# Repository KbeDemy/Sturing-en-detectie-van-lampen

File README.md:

# I2C Uitbreiding bord - Lamp sturing & Detectie

Expansion board voor lampenbeheer. Bedoeld voor gebruik met een externe microcontroller (ESP32) via I2C.

## Specificaties
- **I/O Expander:** MCP23017 (I2C) 
- **Input:** 230V AC detectie via LTV-814 optocouplers.
- **Output:** 30V AC sturing voor Eltako relais via Omron G5V-1 relais.
- **Indicatie:** Debug-LED's voor logica en relaisstatus.

## Pinout & Adressen
- **I2C Adres:** Standaard 0x20 (instelbaar via A0, A1, A2).
- **Signaal/voeding - niveaus:** 
    - 3.3VDC logic
    - 5VDC aansturen relais
    - 30VAC aansturen eltako
    - 230VAC uitlezen status lamp
- **MCP GPA 0-7:** INPUT
- **MCP GPB 0-7:** OUTPUT

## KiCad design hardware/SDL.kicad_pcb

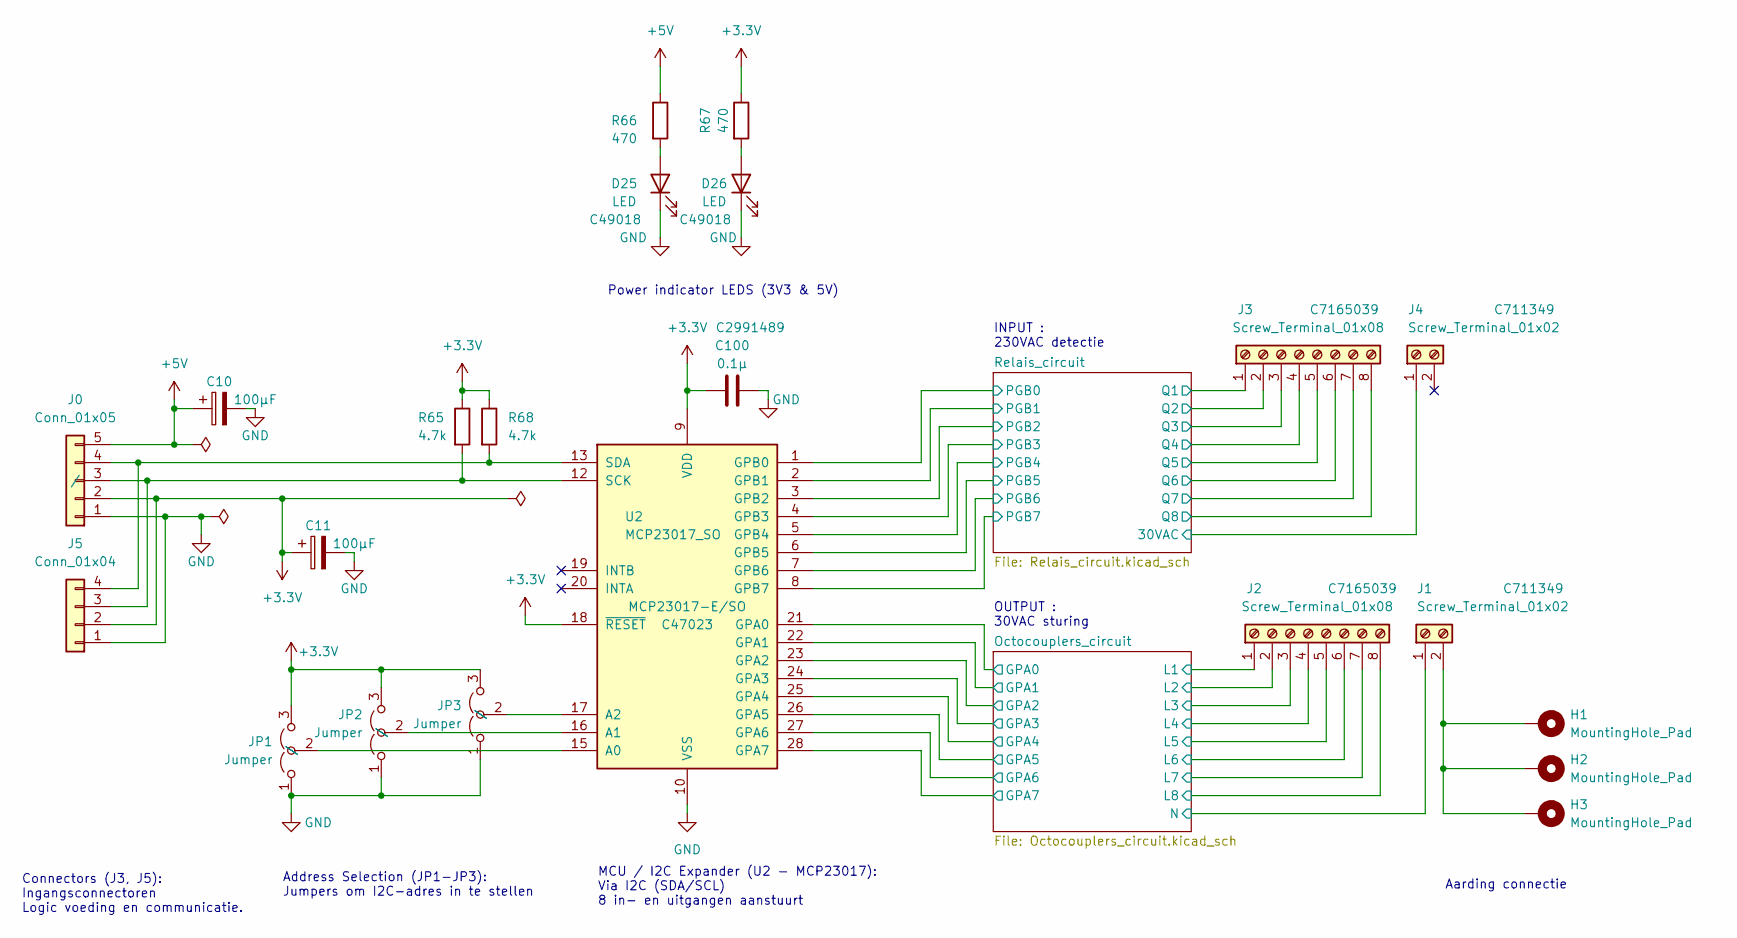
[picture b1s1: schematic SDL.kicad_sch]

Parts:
C10, C11: 100µF; CP_Radial_D4.0mm_P1.50mm
C100: 0.1µ; C_0603_1608Metric; JLCPCB C2991489
D25, D26: LED; LED_0603_1608Metric; JLCPCB C49018
H1, H2, H3: MountingHole_Pad; MountingHole_2.2mm_M2_DIN965_Pad_TopBottom
J0: Conn_01x05; PinSocket_1x05_P2.54mm_Vertical; MPN /; JLCPCB /
J1, J4: Screw_Terminal_01x02; TerminalBlock_Phoenix_MKDS-1,5-2-5.08_1x02_P5.08mm_Horizont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; MPN 1715721; JLCPCB C711349
J2, J3: Screw_Terminal_01x08; TerminalBlock_Phoenix_MKDS-1,5-8-5.08_1x08_P5.08mm_Horizont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; MPN 1715789; JLCPCB C7165039
J5: Conn_01x04; PinHeader_1x04_P2.54mm_Vertical
JP1, JP2, JP3: Jumper; SolderJumper-3_P1.3mm_Open_RoundedPad1.0x1.5mm_NumberLabels; MPN /; JLCPCB /
R65, R68: 4.7k; R_0603_1608Metric
R66, R67: 470; R_0603_1608Metric
U2: MCP23017_SO; SOIC-28W_7.5x17.9mm_P1.27mm; MPN MCP23017-E/SO; JLCPCB C47023

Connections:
+3.3V: C11.1, C100.1, J0.2, J5.2, JP1.3 (B), JP2.3 (B), JP3.3 (B), R65.1, R67.1, R68.1, U2.9 (VDD), U2.18 (~RESET); also elsewhere on the board
+5V: C10.1, J0.5, R66.1; also elsewhere on the board
/Octocouplers_circuit/GPA0: U2.21 (GPA0); also elsewhere on the board
/Octocouplers_circuit/GPA1: U2.22 (GPA1); also elsewhere on the board
/Octocouplers_circuit/GPA2: U2.23 (GPA2); also elsewhere on the board
/Octocouplers_circuit/GPA3: U2.24 (GPA3); also elsewhere on the board
/Octocouplers_circuit/GPA4: U2.25 (GPA4); also elsewhere on the board
/Octocouplers_circuit/GPA5: U2.26 (GPA5); also elsewhere on the board
/Octocouplers_circuit/GPA6: U2.27 (GPA6); also elsewhere on the board
/Octocouplers_circuit/GPA7: U2.28 (GPA7); also elsewhere on the board
/Octocouplers_circuit/L1: J2.1; also elsewhere on the board
/Octocouplers_circuit/L2: J2.2; also elsewhere on the board
/Octocouplers_circuit/L3: J2.3; also elsewhere on the board
/Octocouplers_circuit/L4: J2.4; also elsewhere on the board
/Octocouplers_circuit/L5: J2.5; also elsewhere on the board
/Octocouplers_circuit/L6: J2.6; also elsewhere on the board
/Octocouplers_circuit/L7: J2.7; also elsewhere on the board
/Octocouplers_circuit/L8: J2.8; also elsewhere on the board
/Octocouplers_circuit/N: J1.1; also elsewhere on the board
/Relais_circuit/30VAC: J4.1; also elsewhere on the board
/Relais_circuit/PGB0: U2.1 (GPB0); also elsewhere on the board
/Relais_circuit/PGB1: U2.2 (GPB1); also elsewhere on the board
/Relais_circuit/PGB2: U2.3 (GPB2); also elsewhere on the board
/Relais_circuit/PGB3: U2.4 (GPB3); also elsewhere on the board
/Relais_circuit/PGB4: U2.5 (GPB4); also elsewhere on the board
/Relais_circuit/PGB5: U2.6 (GPB5); also elsewhere on the board
/Relais_circuit/PGB6: U2.7 (GPB6); also elsewhere on the board
/Relais_circuit/PGB7: U2.8 (GPB7); also elsewhere on the board
/Relais_circuit/Q1: J3.1; also elsewhere on the board
/Relais_circuit/Q2: J3.2; also elsewhere on the board
/Relais_circuit/Q3: J3.3; also elsewhere on the board
/Relais_circuit/Q4: J3.4; also elsewhere on the board
/Relais_circuit/Q5: J3.5; also elsewhere on the board
/Relais_circuit/Q6: J3.6; also elsewhere on the board
/Relais_circuit/Q7: J3.7; also elsewhere on the board
/Relais_circuit/Q8: J3.8; also elsewhere on the board
GND: C10.2, C11.2, C100.2, D25.1 (K), D26.1 (K), J0.1, J5.1, JP1.1 (A), JP2.1 (A), JP3.1 (A), U2.10 (VSS); also elsewhere on the board
unnamed: D25.2 (A), R66.2
unnamed: D26.2 (A), R67.2
unnamed: J0.3, J5.3, R65.2, U2.12 (SCK)
unnamed: J0.4, J5.4, R68.2, U2.13 (SDA)
unnamed: H1.1, H2.1, H3.1, J1.2
unnamed: JP1.2 (C), U2.15 (A0)
unnamed: JP2.2 (C), U2.16 (A1)
unnamed: JP3.2 (C), U2.17 (A2)

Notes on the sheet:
INPUT : 230VAC detectie
OUTPUT : 30VAC sturing
MCU / I2C Expander (U2 - MCP23017): Via I2C (SDA/SCL) 8 in- en uitgangen aanstuurt
Connectors (J3, J5): Ingangsconnectoren Logic voeding en communicatie.
Address Selection (JP1-JP3): Jumpers om I2C-adres in te stellen
Aarding connectie
Power indicator LEDS (3V3 & 5V)

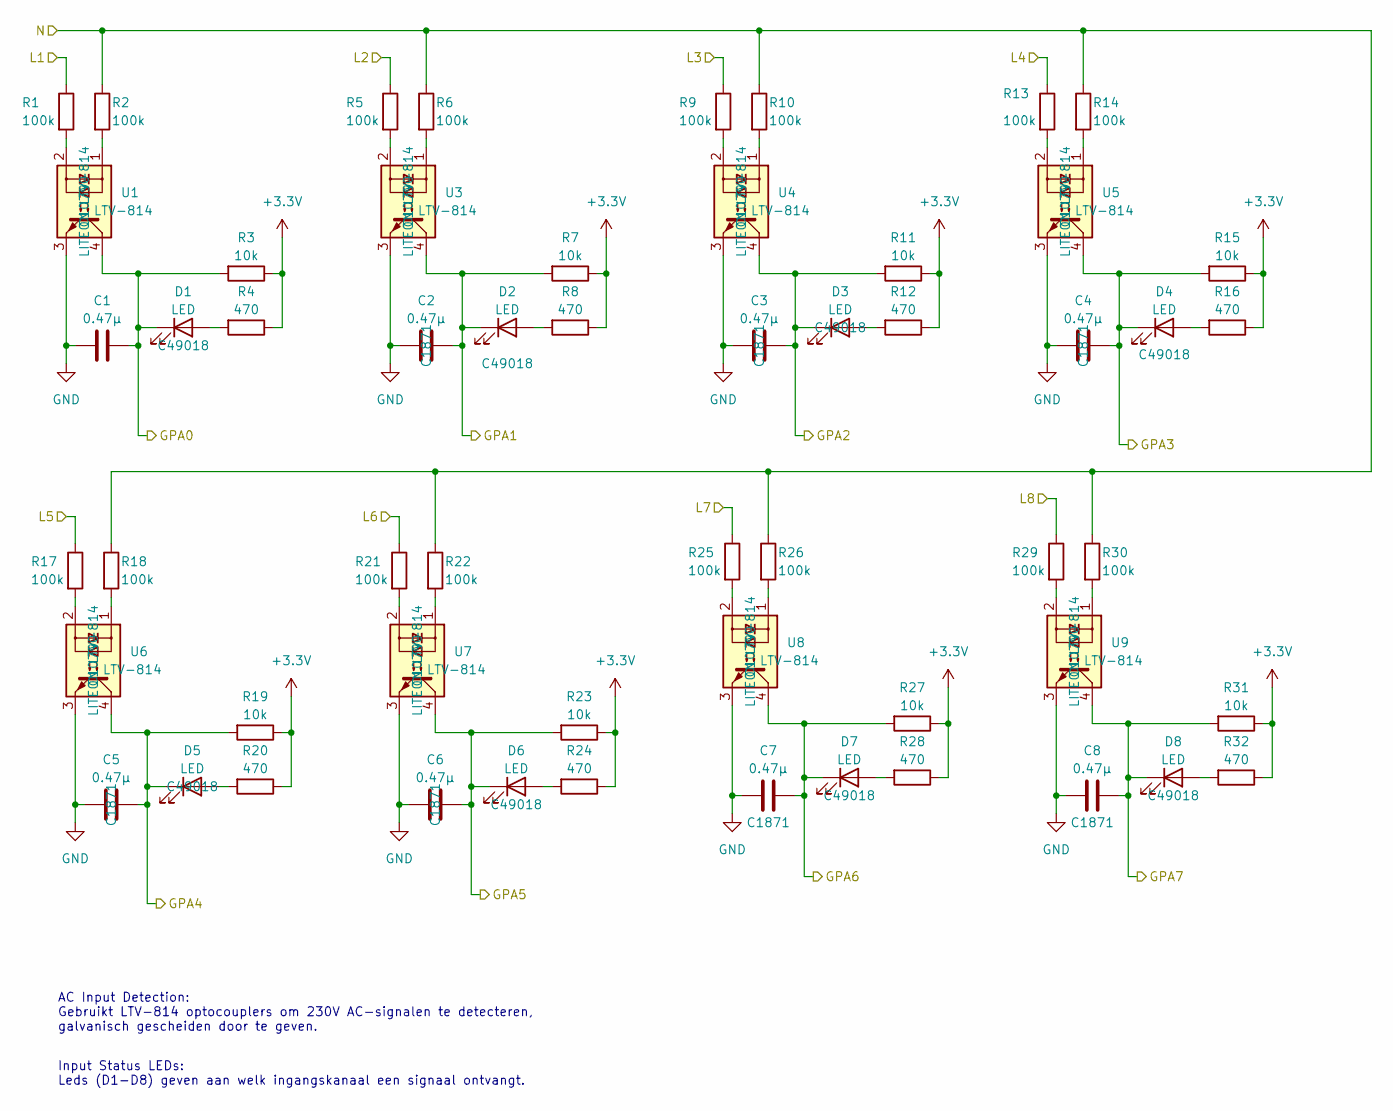
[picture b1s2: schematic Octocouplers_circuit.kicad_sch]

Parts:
C1, C2, C3, C4, C5, C6, C7, C8: 0.47µ; C_0603_1608Metric; JLCPCB C1871
D1, D2, D3, D4, D5, D6, D7, D8: LED; LED_0603_1608Metric; JLCPCB C49018
R1, R2, R5, R6, R9, R10, R13, R14, R17, R18, R21, R22, R25, R26, R29, R30: 100k; R_1206_3216Metric
R3, R7, R11, R15, R19, R23, R27, R31: 10k; R_0603_1608Metric
R4, R8, R12, R16, R20, R24, R28, R32: 470; R_0603_1608Metric
U1, U3, U4, U5, U6, U7, U8, U9: LTV-814; DIP-4_W7.62mm; MPN LITEON LTV-814; JLCPCB C10790

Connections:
+3.3V: R3.1, R4.1, R7.1, R8.1, R11.1, R12.1, R15.1, R16.1, R19.1, R20.1, R23.1, R24.1, R27.1, R28.1, R31.1, R32.1; also elsewhere on the board
/Octocouplers_circuit/GPA0: C1.2, D1.1 (K), R3.2, U1.4; also elsewhere on the board
/Octocouplers_circuit/GPA1: C2.2, D2.1 (K), R7.2, U3.4; also elsewhere on the board
/Octocouplers_circuit/GPA2: C3.2, D3.1 (K), R11.2, U4.4; also elsewhere on the board
/Octocouplers_circuit/GPA3: C4.2, D4.1 (K), R15.2, U5.4; also elsewhere on the board
/Octocouplers_circuit/GPA4: C5.2, D5.1 (K), R19.2, U6.4; also elsewhere on the board
/Octocouplers_circuit/GPA5: C6.2, D6.1 (K), R23.2, U7.4; also elsewhere on the board
/Octocouplers_circuit/GPA6: C7.2, D7.1 (K), R27.2, U8.4; also elsewhere on the board
/Octocouplers_circuit/GPA7: C8.2, D8.1 (K), R31.2, U9.4; also elsewhere on the board
/Octocouplers_circuit/L1: R1.1; also elsewhere on the board
/Octocouplers_circuit/L2: R5.1; also elsewhere on the board
/Octocouplers_circuit/L3: R9.1; also elsewhere on the board
/Octocouplers_circuit/L4: R13.1; also elsewhere on the board
/Octocouplers_circuit/L5: R17.1; also elsewhere on the board
/Octocouplers_circuit/L6: R21.1; also elsewhere on the board
/Octocouplers_circuit/L7: R25.1; also elsewhere on the board
/Octocouplers_circuit/L8: R29.1; also elsewhere on the board
/Octocouplers_circuit/N: R2.1, R6.1, R10.1, R14.1, R18.1, R22.1, R26.1, R30.1; also elsewhere on the board
GND: C1.1, C2.1, C3.1, C4.1, C5.1, C6.1, C7.1, C8.1, U1.3, U3.3, U4.3, U5.3, U6.3, U7.3, U8.3, U9.3; also elsewhere on the board
unnamed: D1.2 (A), R4.2
unnamed: D2.2 (A), R8.2
unnamed: D3.2 (A), R12.2
unnamed: D4.2 (A), R16.2
unnamed: D5.2 (A), R20.2
unnamed: D6.2 (A), R24.2
unnamed: D7.2 (A), R28.2
unnamed: D8.2 (A), R32.2
unnamed: R1.2, U1.2
unnamed: R2.2, U1.1
unnamed: R5.2, U3.2
unnamed: R6.2, U3.1
unnamed: R9.2, U4.2
unnamed: R10.2, U4.1
unnamed: R13.2, U5.2
unnamed: R14.2, U5.1
unnamed: R17.2, U6.2
unnamed: R18.2, U6.1
unnamed: R21.2, U7.2
unnamed: R22.2, U7.1
unnamed: R25.2, U8.2
unnamed: R26.2, U8.1
unnamed: R29.2, U9.2
unnamed: R30.2, U9.1

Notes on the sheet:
AC Input Detection: Gebruikt LTV-814 optocouplers om 230V AC-signalen te detecteren, galvanisch gescheiden door te geven.
Input Status LEDs: Leds (D1-D8) geven aan welk ingangskanaal een signaal ontvangt.

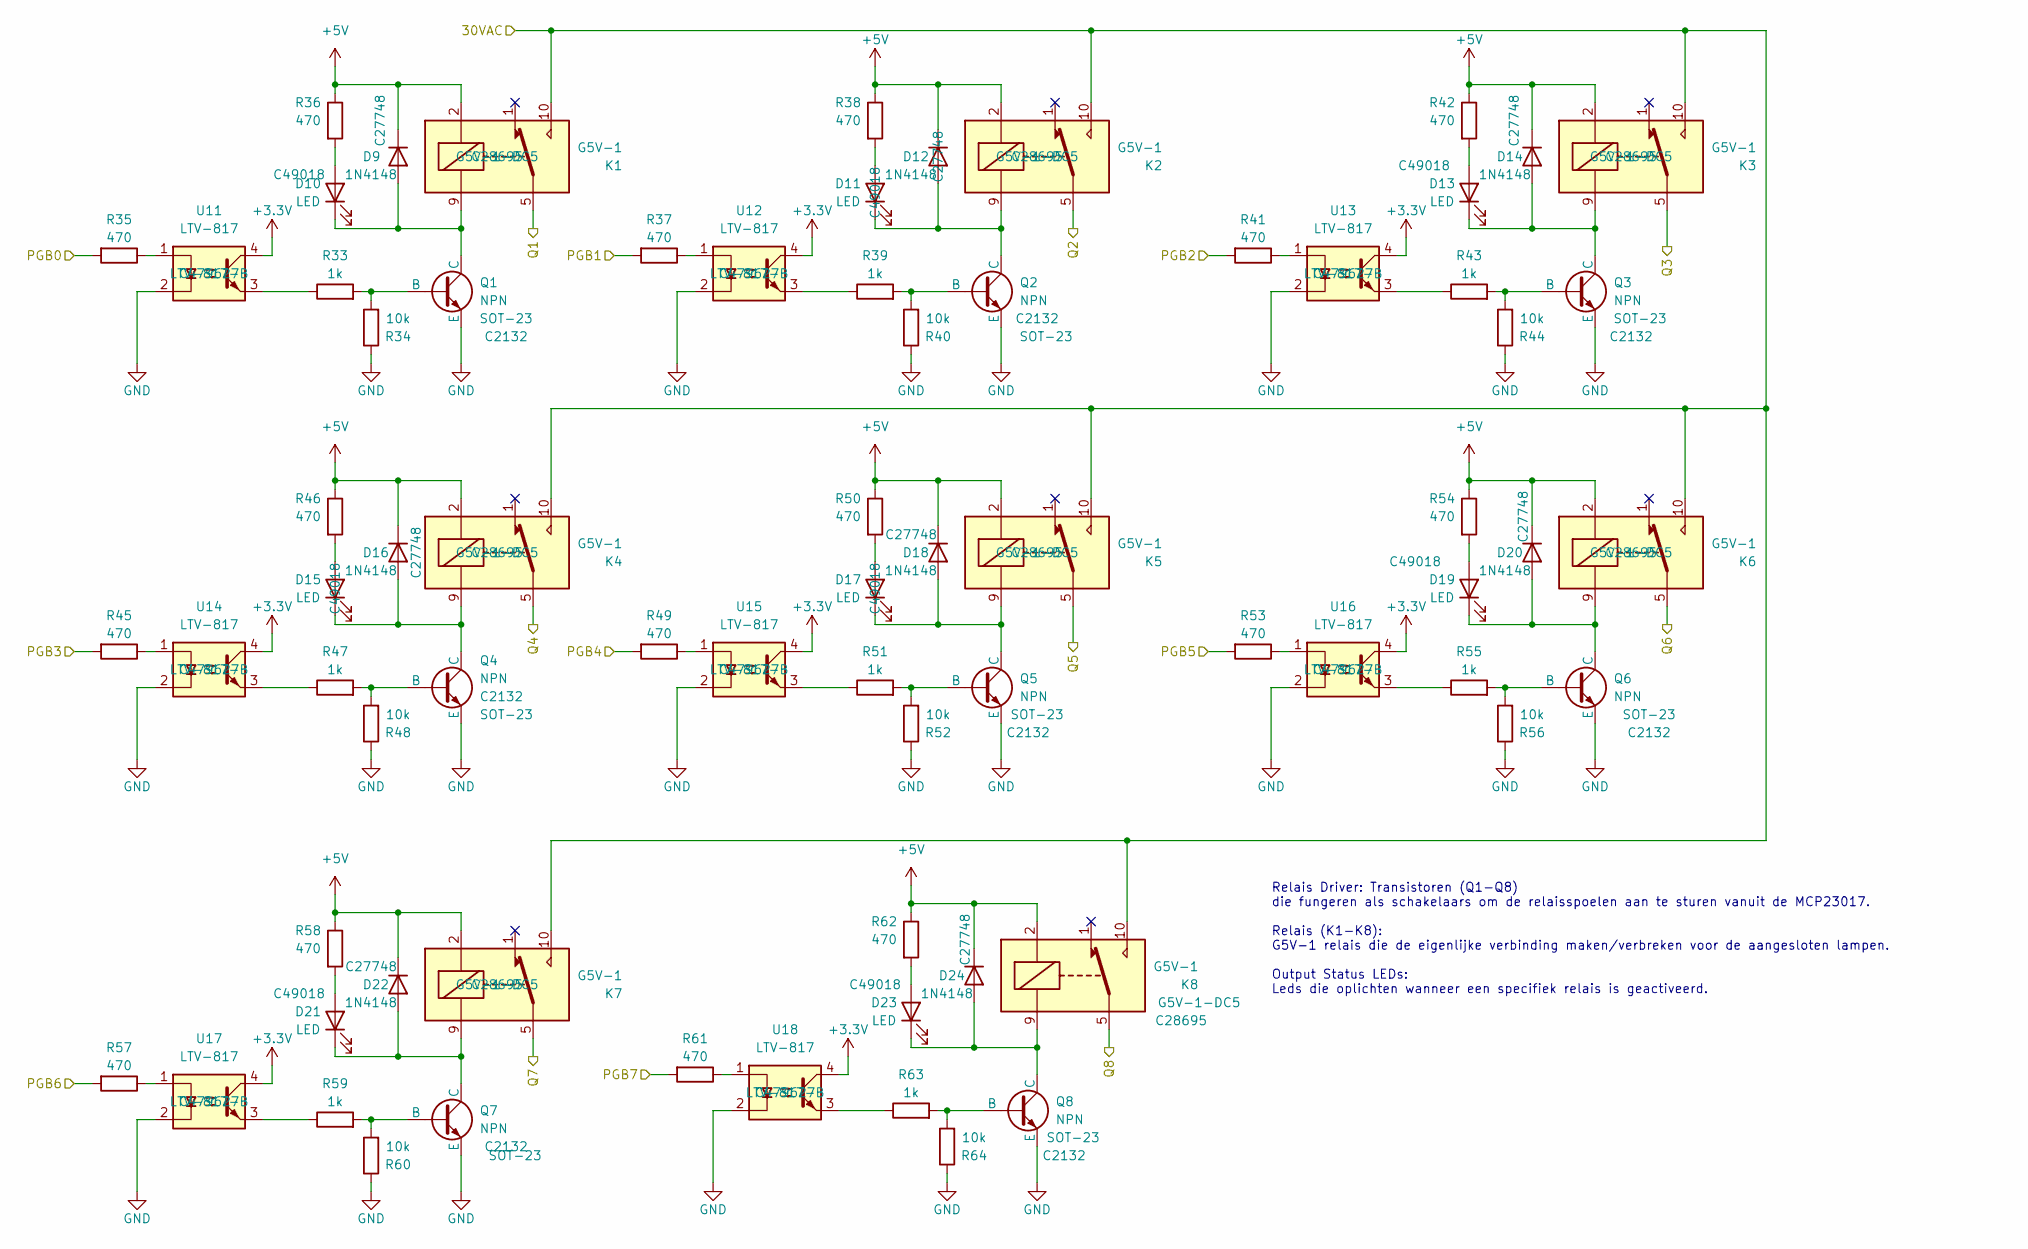
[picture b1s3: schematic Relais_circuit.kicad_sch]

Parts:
D9, D12, D14, D16, D18, D20, D22, D24: 1N4148; D_SOD-523; JLCPCB C27748
D10, D11, D13, D15, D17, D19, D21, D23: LED; LED_0603_1608Metric; JLCPCB C49018
K1, K2, K3, K4, K5, K6, K7, K8: G5V-1; Relay_SPDT_Omron_G5V-1; MPN G5V-1-DC5; JLCPCB C28695
Q1, Q2, Q3, Q4, Q5, Q6, Q7, Q8: NPN; SOT-23; MPN SOT-23; JLCPCB C2132
R33, R39, R43, R47, R51, R55, R59, R63: 1k; R_0603_1608Metric
R34, R40, R44, R48, R52, R56, R60, R64: 10k; R_0603_1608Metric
R35, R36, R37, R38, R41, R42, R45, R46, R49, R50, R53, R54, R57, R58, R61, R62: 470; R_0603_1608Metric
U11, U12, U13, U14, U15, U16, U17, U18: LTV-817; DIP-4_W7.62mm; MPN LTV-817-B; JLCPCB C479627

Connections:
+3.3V: U11.4, U12.4, U13.4, U14.4, U15.4, U16.4, U17.4, U18.4; also elsewhere on the board
+5V: D9.1 (K), D12.1 (K), D14.1 (K), D16.1 (K), D18.1 (K), D20.1 (K), D22.1 (K), D24.1 (K), K1.2, K2.2, K3.2, K4.2, K5.2, K6.2, K7.2, K8.2, R36.1, R38.1, R42.1, R46.1, R50.1, R54.1, R58.1, R62.1; also elsewhere on the board
/Relais_circuit/30VAC: K1.10, K2.10, K3.10, K4.10, K5.10, K6.10, K7.10, K8.10; also elsewhere on the board
/Relais_circuit/PGB0: R35.2; also elsewhere on the board
/Relais_circuit/PGB1: R37.2; also elsewhere on the board
/Relais_circuit/PGB2: R41.2; also elsewhere on the board
/Relais_circuit/PGB3: R45.2; also elsewhere on the board
/Relais_circuit/PGB4: R49.2; also elsewhere on the board
/Relais_circuit/PGB5: R53.2; also elsewhere on the board
/Relais_circuit/PGB6: R57.2; also elsewhere on the board
/Relais_circuit/PGB7: R61.2; also elsewhere on the board
/Relais_circuit/Q1: K1.5, K1.6; also elsewhere on the board
/Relais_circuit/Q2: K2.5, K2.6; also elsewhere on the board
/Relais_circuit/Q3: K3.5, K3.6; also elsewhere on the board
/Relais_circuit/Q4: K4.5, K4.6; also elsewhere on the board
/Relais_circuit/Q5: K5.5, K5.6; also elsewhere on the board
/Relais_circuit/Q6: K6.5, K6.6; also elsewhere on the board
/Relais_circuit/Q7: K7.5, K7.6; also elsewhere on the board
/Relais_circuit/Q8: K8.5, K8.6; also elsewhere on the board
GND: Q1.2 (E), Q2.2 (E), Q3.2 (E), Q4.2 (E), Q5.2 (E), Q6.2 (E), Q7.2 (E), Q8.2 (E), R34.1, R40.1, R44.1, R48.1, R52.1, R56.1, R60.1, R64.1, U11.2, U12.2, U13.2, U14.2, U15.2, U16.2, U17.2, U18.2; also elsewhere on the board
unnamed: D10.2 (A), R36.2
unnamed: D9.2 (A), D10.1 (K), K1.9, Q1.3 (C)
unnamed: D11.2 (A), R38.2
unnamed: D11.1 (K), D12.2 (A), K2.9, Q2.3 (C)
unnamed: D13.2 (A), R42.2
unnamed: D13.1 (K), D14.2 (A), K3.9, Q3.3 (C)
unnamed: D15.2 (A), R46.2
unnamed: D15.1 (K), D16.2 (A), K4.9, Q4.3 (C)
unnamed: D17.2 (A), R50.2
unnamed: D17.1 (K), D18.2 (A), K5.9, Q5.3 (C)
unnamed: D19.2 (A), R54.2
unnamed: D19.1 (K), D20.2 (A), K6.9, Q6.3 (C)
unnamed: D21.2 (A), R58.2
unnamed: D21.1 (K), D22.2 (A), K7.9, Q7.3 (C)
unnamed: D23.2 (A), R62.2
unnamed: D23.1 (K), D24.2 (A), K8.9, Q8.3 (C)
unnamed: Q1.1 (B), R33.2, R34.2
unnamed: Q2.1 (B), R39.2, R40.2
unnamed: Q3.1 (B), R43.2, R44.2
unnamed: Q4.1 (B), R47.2, R48.2
unnamed: Q5.1 (B), R51.2, R52.2
unnamed: Q6.1 (B), R55.2, R56.2
unnamed: Q7.1 (B), R59.2, R60.2
unnamed: Q8.1 (B), R63.2, R64.2
unnamed: R33.1, U11.3
unnamed: R35.1, U11.1
unnamed: R37.1, U12.1
unnamed: R39.1, U12.3
unnamed: R41.1, U13.1
unnamed: R43.1, U13.3
unnamed: R45.1, U14.1
unnamed: R47.1, U14.3
unnamed: R49.1, U15.1
unnamed: R51.1, U15.3
unnamed: R53.1, U16.1
unnamed: R55.1, U16.3
unnamed: R57.1, U17.1
unnamed: R59.1, U17.3
unnamed: R61.1, U18.1
unnamed: R63.1, U18.3

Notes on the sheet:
Relais Driver: Transistoren (Q1-Q8) die fungeren als schakelaars om de relaisspoelen aan te sturen vanuit de MCP23017. Relais (K1-K8): G5V-1 relais die de eigenlijke verbinding maken/verbreken voor de aangesloten lampen. Output Status LEDs: Leds die oplichten wanneer een specifiek relais is geactiv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

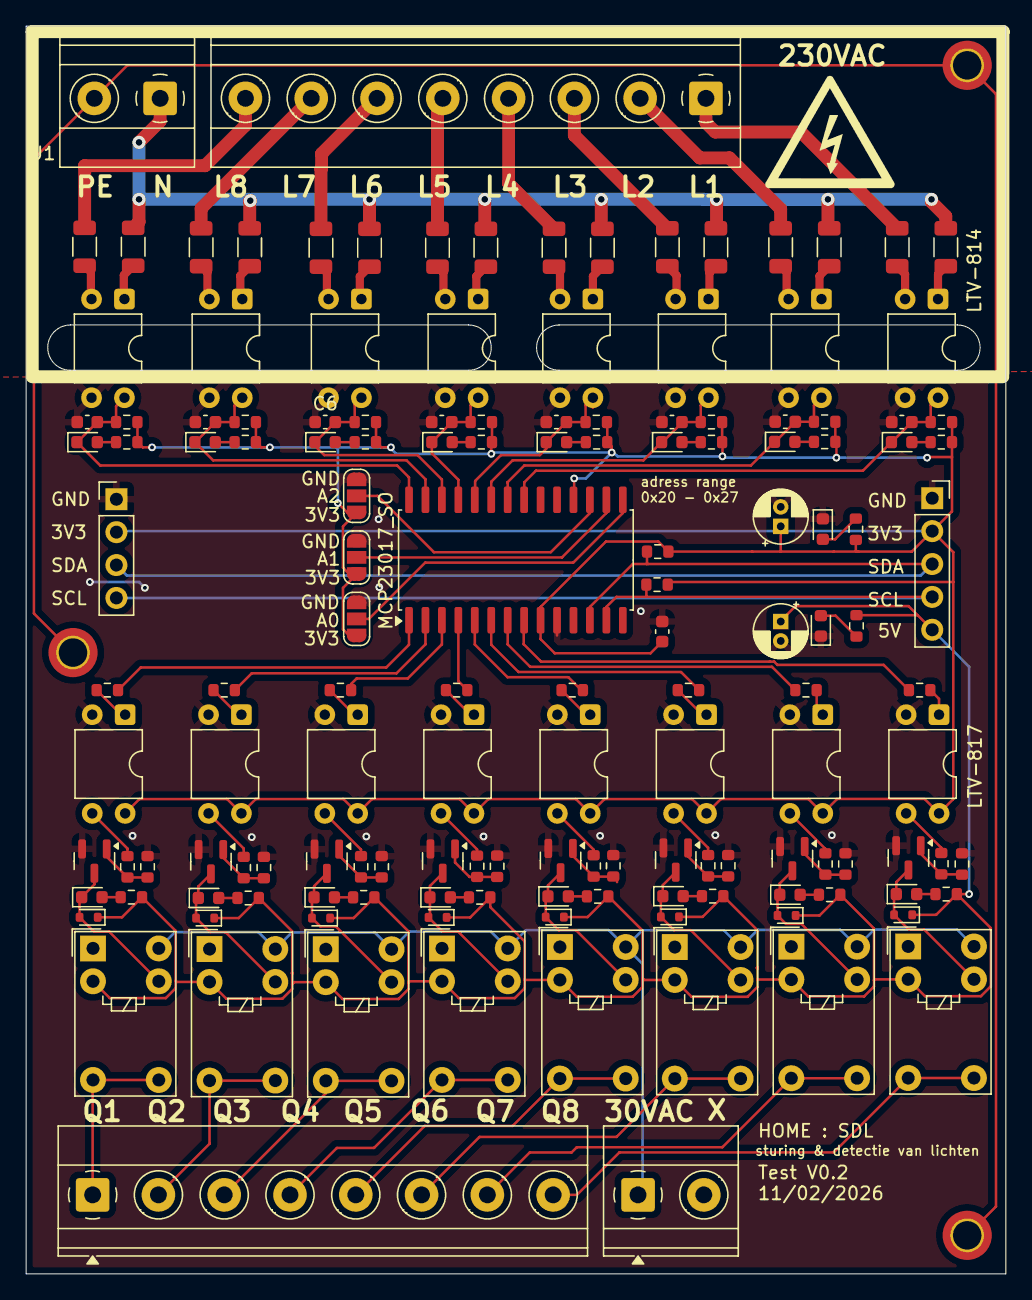
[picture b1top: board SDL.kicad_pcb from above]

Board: 4 copper layers, 75.6 x 96.3 mm, 151 parts (1 on the bottom side), 109 nets.

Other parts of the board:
GITHUB: DOCS; https___github.com_KbeDemy_Sturing-en-detectie-van-lampen

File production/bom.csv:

Designator,Footprint,Quantity,Value,LCSC Part #
"C1, C2, C3, C4, C5, C6, C7, C8",0603,8,0.47µ,CC0603KRX7R9BB474 
"C10, C11",CP_Radial_D4.0mm_P1.50mm,2,100µF,
C100,0603,1,0.1µ,CC0603KRX7R9BB104
"D1, D10, D11, D13, D15, D17, D19, D2, D21, D23, D25, D26, D3, D4, D5, D6, D7, D8",0603,18,LED,XL-1608SURC-06 
"D12, D14, D16, D18, D20, D22, D24, D9",D_SOD-523,8,1N4148,1N4148WT 
GITHUB,https___github.com_KbeDemy_Sturing-en-detectie-van-lampen,1,DOCS,
J0,PinSocket_1x05_P2.54mm_Vertical,1,Conn_01x05,
"J1, J4","TerminalBlock_Phoenix_MKDS-1,5-2-5.08_1x02_P5.08mm_Horizontal",2,Screw_Terminal_01x02,1715721 
"J2, J3","TerminalBlock_Phoenix_MKDS-1,5-8-5.08_1x08_P5.08mm_Horizontal",2,Screw_Terminal_01x08,1715789
J5,PinHeader_1x04_P2.54mm_Vertical,1,Conn_01x04,
"K1, K2, K3, K4, K5, K6, K7, K8",Relay_SPDT_Omron_G5V-1,8,G5V-1,G5V-1-DC5 
"Q1, Q2, Q3, Q4, Q5, Q6, Q7, Q8",SOT-23,8,NPN,MMBT5551
"R1, R10, R13, R14, R17, R18, R2, R21, R22, R25, R26, R29, R30, R5, R6, R9",1206,16,100k,RC1206FR-7W100KL
"R11, R15, R19, R23, R27, R3, R31, R34, R40, R44, R48, R52, R56, R60, R64, R7",0603,16,10k,RC0603FR-0710KL
"R12, R16, R20, R24, R28, R32, R35, R36, R37, R38, R4, R41, R42, R45, R46, R49, R50, R53, R54, R57, R58, R61, R62, R66, R67, R8",0603,26,470,0603WAF4700T5E
"R33, R39, R43, R47, R51, R55, R59, R63",0603,8,1k,RC0603FR-071KL
"R65, R68",0603,2,4.7k,FRC0603J472 TS
"U1, U3, U4, U6, U7, U8, U9",DIP-4_W7.62mm,7,LTV-814,LITEON LTV-814
"U11, U12, U13, U14, U15, U16, U17, U18",DIP-4_W7.62mm,8,LTV-817,LTV-817-B
U2,SOIC-28W_7.5x17.9mm_P1.27mm,1,MCP23017_SO,MCP23017-E/SO
U5,DIP-4_W7.62mm,1,LTV-814,

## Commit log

2026-02-13 Revise README for I2C expansion board details
    Updated project title and added specifications for the I2C expansion board.
2026-02-13 Update signal/power levels section in README
2026-02-14 Add Bill of Materials section to readme
    Added a Bill of Materials (BOM) section with component details, including values, descriptions, package types, LCSC codes, and datasheets.
2026-02-14 Add PCB specifications to readme
2026-02-14 Create images
2026-02-14 Rename readme.md to BOM.md
2026-02-20 Update relay control description in README
